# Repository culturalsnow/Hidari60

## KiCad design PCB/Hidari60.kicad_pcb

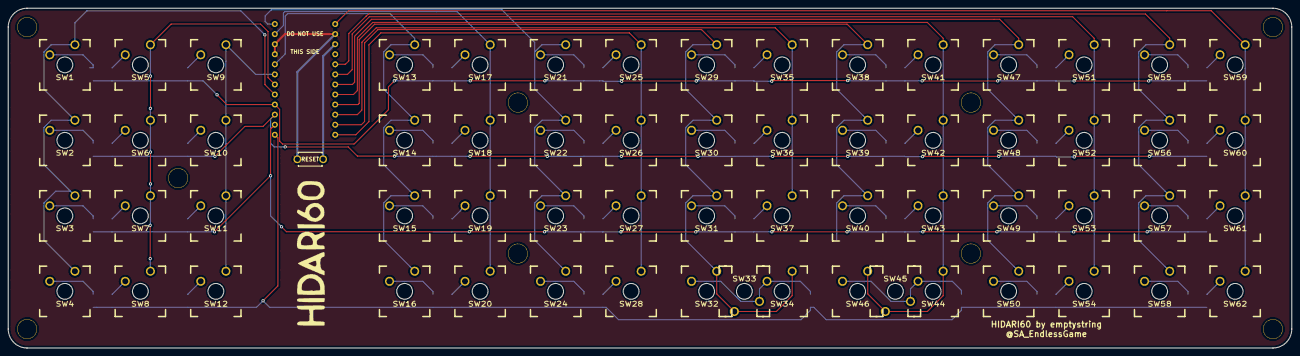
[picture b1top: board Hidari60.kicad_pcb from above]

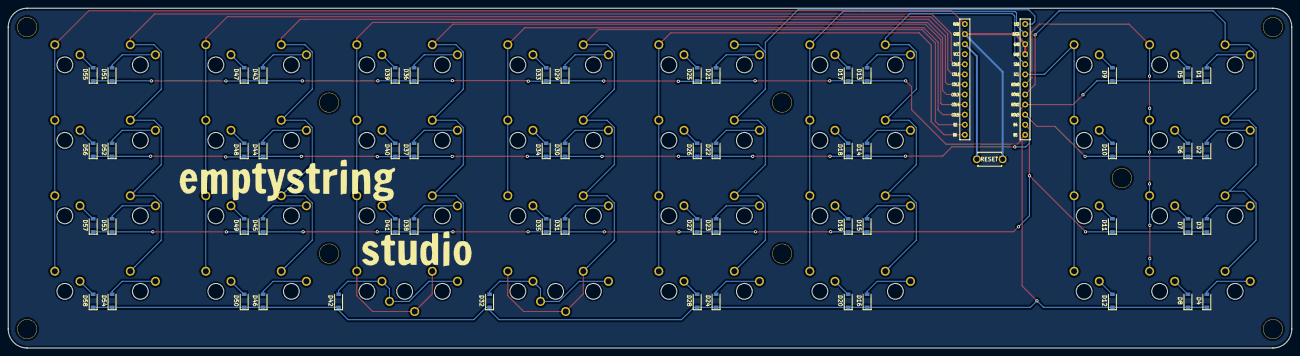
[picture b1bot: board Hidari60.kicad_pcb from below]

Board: 2 copper layers, 323.9 x 85.7 mm, 131 parts (59 on the bottom side), 79 nets.

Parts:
D1, D2, D3, D4, D5, D6, D7, D8, D9, D10, D11, D12, D13, D14, D15, D16, D17, D18, D19, D20, D21, D22, D23, D24, D25, D26, D27, D28, D29, D30, D31, D32, D33, D34, D35, D36, D37, D38, D39, D40, D41, D42, D43, D44, D45, D46, D47, D48, D49, D50, D51, D52, D53, D54, D55, D56, D57, D58: D; D_SOD-123
Ref**: Val**; HOLE
Ref**#2, Ref**#3, Ref**#4, Ref**#5, Ref**#6, Ref**#7, Ref**#8, Ref**#9: Val**; HOLE
SW1, SW2, SW3, SW4, SW5, SW6, SW7, SW8, SW9, SW10, SW11, SW12, SW13, SW14, SW15, SW16, SW17, SW18, SW19, SW20, SW21, SW22, SW23, SW24, SW25, SW26, SW27, SW28, SW29, SW30, SW31, SW32, SW33, SW34, SW35, SW36, SW37, SW38, SW39, SW40, SW41, SW42, SW43, SW44, SW45, SW46, SW47, SW48, SW49, SW50, SW51, SW52, SW53, SW54, SW55, SW56, SW57, SW58, SW59, SW60, SW61, SW62: SW_PUSH; MX_Plate_100H
SW63: SW_PUSH; ResetSW
U1: ProMicro; ProMicro_v2_Backside

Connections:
GND: SW63.2, U1.3, U1.4, U1.23
unnamed: D1.2, SW1.2
unnamed: D2.2, SW2.2
unnamed: D3.2, SW3.2
unnamed: D4.2, SW4.2
unnamed: D5.2, SW5.2
unnamed: D6.2, SW6.2
unnamed: D7.2, SW7.2
unnamed: D8.2, SW8.2
unnamed: D9.2, SW9.2
unnamed: D10.2, SW10.2
unnamed: D11.2, SW11.2
unnamed: D12.2, SW12.2
unnamed: D13.2, SW13.2
unnamed: D14.2, SW14.2
unnamed: D15.2, SW15.2
unnamed: D16.2, SW16.2
unnamed: D17.2, SW17.2
unnamed: D18.2, SW18.2
unnamed: D19.2, SW19.2
unnamed: D20.2, SW20.2
unnamed: D21.2, SW21.2
unnamed: D22.2, SW22.2
unnamed: D23.2, SW23.2
unnamed: D24.2, SW24.2
unnamed: D25.2, SW25.2
unnamed: D26.2, SW26.2
unnamed: D27.2, SW27.2
unnamed: D28.2, SW28.2
unnamed: D29.2, SW29.2
unnamed: D30.2, SW30.2
unnamed: D31.2, SW31.2
unnamed: D32.2, SW32.2, SW33.2, SW34.2
unnamed: D33.2, SW35.2
unnamed: D34.2, SW36.2
unnamed: D35.2, SW37.2
unnamed: D36.2, SW38.2
unnamed: D37.2, SW39.2
unnamed: D38.2, SW40.2
unnamed: D39.2, SW41.2
unnamed: D40.2, SW42.2
unnamed: D41.2, SW43.2
unnamed: D42.2, SW44.2, SW45.2, SW46.2
unnamed: D43.2, SW47.2
unnamed: D44.2, SW48.2
unnamed: D45.2, SW49.2
unnamed: D46.2, SW50.2
unnamed: D47.2, SW51.2
unnamed: D48.2, SW52.2
unnamed: D49.2, SW53.2
unnamed: D50.2, SW54.2
unnamed: D51.2, SW55.2
unnamed: D52.2, SW56.2
unnamed: D53.2, SW57.2
unnamed: D54.2, SW58.2
unnamed: D55.2, SW59.2
unnamed: D56.2, SW60.2
unnamed: D57.2, SW61.2
unnamed: D58.2, SW62.2
c0: SW1.1, SW2.1, SW3.1, SW4.1, U1.8
c1: SW5.1, SW6.1, SW7.1, SW8.1, U1.7
c2: SW9.1, SW10.1, SW11.1, SW12.1, U1.6
c3: SW13.1, SW14.1, SW15.1, SW16.1, U1.5
c4: SW17.1, SW18.1, SW19.1, SW20.1, U1.2
c5: SW21.1, SW22.1, SW23.1, SW24.1, U1.1
c6: SW25.1, SW26.1, SW27.1, SW28.1, U1.13
c7: SW29.1, SW30.1, SW31.1, SW32.1, SW33.1, SW34.1, U1.14
c8: SW35.1, SW36.1, SW37.1, U1.15
c9: SW38.1, SW39.1, SW40.1, U1.16
c10: SW41.1, SW42.1, SW43.1, SW44.1, SW45.1, SW46.1, U1.17
c11: SW47.1, SW48.1, SW49.1, SW50.1, U1.18
c12: SW51.1, SW52.1, SW53.1, SW54.1, U1.19
c13: SW55.1, SW56.1, SW57.1, SW58.1, U1.20
c14: SW59.1, SW60.1, SW61.1, SW62.1, U1.24
r0: D1.1, D5.1, D9.1, D13.1, D17.1, D21.1, D25.1, D29.1, D33.1, D36.1, D39.1, D43.1, D47.1, D51.1, D55.1, U1.9
r1: D2.1, D6.1, D10.1, D14.1, D18.1, D22.1, D26.1, D30.1, D34.1, D37.1, D40.1, D44.1, D48.1, D52.1, D56.1, U1.10
r2: D3.1, D7.1, D11.1, D15.1, D19.1, D23.1, D27.1, D31.1, D35.1, D38.1, D41.1, D45.1, D49.1, D53.1, D57.1, U1.11
r3: D4.1, D8.1, D12.1, D16.1, D20.1, D24.1, D28.1, D32.1, D42.1, D46.1, D50.1, D54.1, D58.1, U1.12
reset: SW63.1, U1.22

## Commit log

2019-03-24 pcb finished
2019-03-24 directory for pcb
